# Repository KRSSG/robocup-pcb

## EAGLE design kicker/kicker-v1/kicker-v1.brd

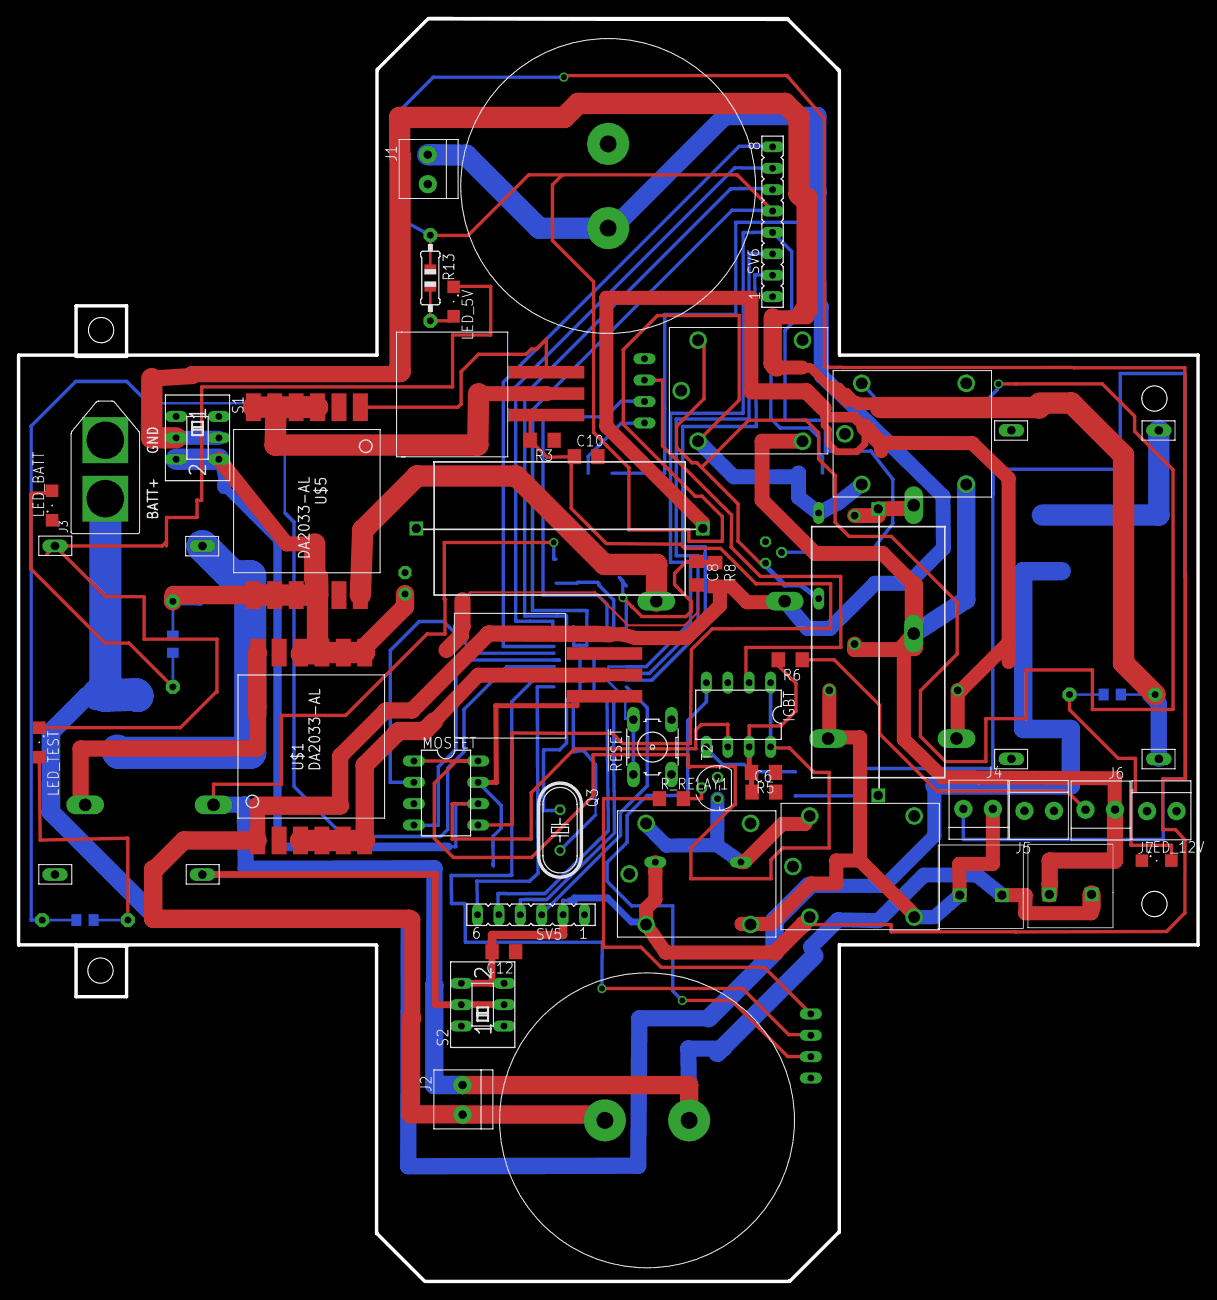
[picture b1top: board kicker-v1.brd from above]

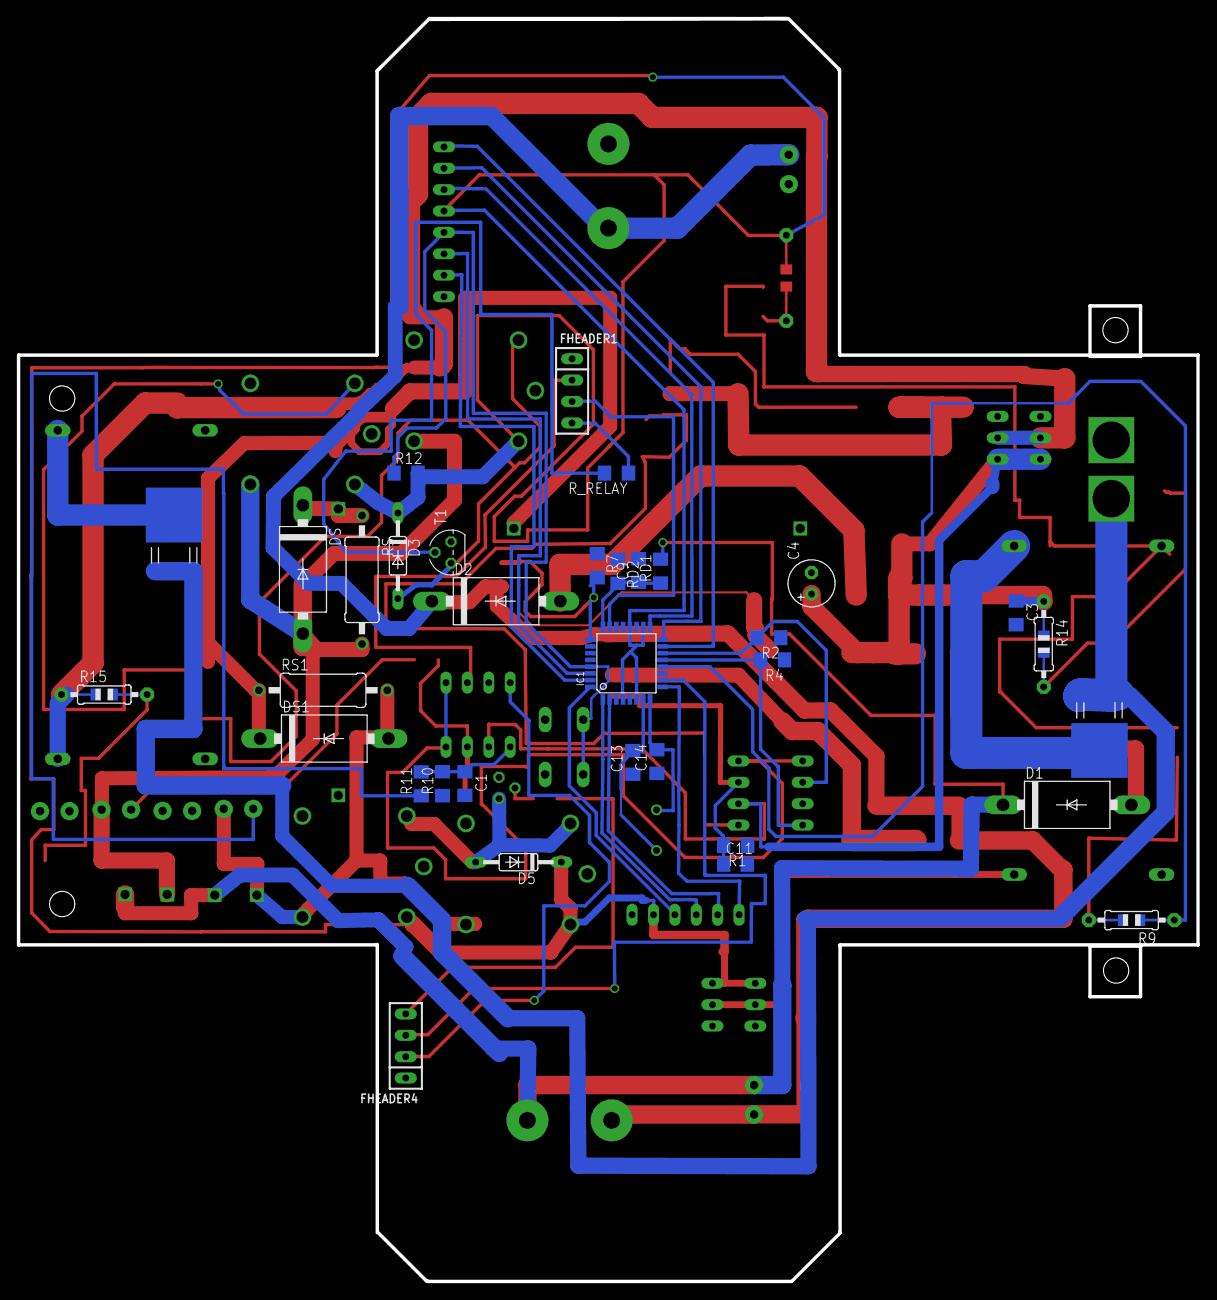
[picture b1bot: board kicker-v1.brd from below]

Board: 2 copper layers, 140.0 x 149.9 mm, 86 parts (34 on the bottom side), 57 nets.

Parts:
5V: PINHEAD_1
!RESET: B3F-10XX
C1, C6, C8, C9, C10, C11: 0.01uF; C1206
C3: 4.7uF; C1206
C4: 4.7uF; E2,5-6
C12: 0.1uF; C1206
C13, C14: 22pF; C1206
D1, D2: UF5400; DO201-15
D3, D5: 1N4446; DO35-10
DS, DS1: UF5400; DO201-15
FHEADER1, FHEADER4: F-1X04-SIP-100-32Y; SIP-100-04-32Y
GND, GND12: PINHEAD_1
GND_5V, GND_12V1: PINHEAD_1
IC1: MEGA8-AI; TQFP32-08
IGBT: NE555; DIL-08
J1, J2, J4, J5, J6, J7: 1X2-3.5MM
J3: XT-60BATT_LABEL; XT-60
LED_5V, LED_12V: SML1206
LED_BATT: SML1206
LED_TEST: SML1206
MOSFET: NE555; DIL-08
POWER_1: PINHEAD_1
POWER_HEAD1: PINHEAD_1
Q3: 16MHz; HC49U70
R1, R3: 1K; R1206
R2, R4, R5, R10, R12: 10K; R1206
R6, R11: 330; R1206
R7: 8.2K; R1206
R8: 1M; R1206
R9, R13: 1 K; 0805-THM
R14, R15: 4.7 K; 0805-THM
RD1: 1M; R1206
RD2: 8.2K; R1206
RS, RS1: 10/.5W; 0411/15
R_RELAY, R_RELAY1: 1K; R1206
S1, S2: A68-A31
SV5: FE06
SV6: FE08
T1, T2: BC547; TO92
U1, U4: TO228P1042X238-3N
U$1, U$5: DA2033-AL
U$2, U$4: CAP
U$3, U$9: MOS
U$6, U$16: SCREW
U$7, U$8: POLYCAP
U$10, U$11, U$12, U$13: REL
V_BAT: PINHEAD_1

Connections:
!RESET: !RESET.1, !RESET.2, IC1.29, R12.1, SV6.4
ATMEGA_POW: C12.2, D3.C, D5.C, IC1.4, IC1.6, IC1.18, IC1.20, R12.2, R13.1, S2.3, S2.6, SV5.2, SV6.5, U$10.2, U$11.2, U$12.2, U$13.2
ATMEGA_POW_BS: 5V.P$1, S2.2, S2.5
BATT: C3.1, C4.+, IGBT.6, MOSFET.6, R14.1, S1.3, S1.6, U$1.P$7, U$1.P$8, U$1.P$9, U$1.P$10, U$5.P$7, U$5.P$8, U$5.P$9, U$5.P$10
C1+: D1.C, J2.1, RD1.2, U$2.P$2, U$6.+, U$16.+
C1-: D2.C, J1.1, J2.2, R8.2, U$1.P$1, U$2.P$1, U$4.P$2
COLLECTOR: D3.A, T1.3, U$10.1, U$12.1
COLLECTOR1: D5.A, T2.3, U$11.1, U$13.1
DRV_IN: J6.2, R6.1
DRV_IN1: J4.2, R11.1
EXT1: IC1.32, SV5.3
EXT2: IC1.1, SV5.4
FEED1: C9.1, IC1.24, RD1.1, RD2.2
FEED2: C8.1, IC1.25, R7.2, R8.1
GND: !RESET.3, !RESET.4, C1.2, C3.2, C4.-, C6.2, C8.2, C9.2, C10.2, C11.2, C12.1, C13.1, C14.1, FHEADER1.1, FHEADER4.1, GND12.P$1, GND_5V.P$1, GND_12V1.P$1, IC1.3, IC1.5, IC1.21, IGBT.3, J1.2, J3.GND, J5.1, J7.1, LED_12V.C, LED_BATT.C, MOSFET.3, R1.1, R2.1, R3.1, R4.1, R5.1, R7.1, R10.1, RD2.1, SV5.1, SV6.1, T1.1, T2.1, U$3.SOURCE, U$4.P$1, U$5.P$1, U$7.2, U$8.2, U$9.SOURCE, U$10.C, U$11.C, U$12.C, U$13.C
GND1: GND.P$1, LED_5V.C, LED_TEST.C
GPIO: IC1.2, SV5.5
GPIO1: IC1.9, SV5.6
IGBT1: FHEADER1.2, IGBT.2
IGBT2: FHEADER4.2, IGBT.4
MISO16: IC1.16, SV6.7
MOS1: IC1.14, MOSFET.2, R2.2
MOS2: IC1.13, MOSFET.4, R4.2
MOSI15: IC1.15, SV6.8
unnamed: DS.C, RS.1, U$7.1
unnamed: R_RELAY.2, T1.2
unnamed: C6.1, IGBT.7, R5.2, R6.2
unnamed: D2.A, U$5.P$12
unnamed: LED_5V.A, R13.2
unnamed: POWER_HEAD1.P$1, U1.2
unnamed: D1.A, U$1.P$12
unnamed: DS1.C, RS1.1, U$8.1
unnamed: R_RELAY1.2, T2.2
unnamed: LED_BATT.A, R14.2
unnamed: C13.2, IC1.7, Q3.2
unnamed: LED_12V.A, R15.2
unnamed: U4.2, V_BAT.P$1
unnamed: C14.2, IC1.8, Q3.1
unnamed: LED_TEST.A, R9.2
unnamed: U$5.P$3, U$5.P$4, U$5.P$5, U$5.P$6, U$9.DRAIN
unnamed: U$1.P$3, U$1.P$4, U$1.P$5, U$1.P$6, U$3.DRAIN
unnamed: IC1.12, R9.1
NC: IGBT.1, IGBT.8, MOSFET.1, MOSFET.8
OUTB: C1.1, IGBT.5, R10.2, R11.2
POWER: POWER_1.P$1, R15.1, S1.2, S1.5
POWER_HEAD: J3.BATT, U1.1, U1.3, U4.1, U4.3
PWM1: C11.1, MOSFET.7, R1.2, U$3.GATE
PWM2: C10.1, MOSFET.5, R3.2, U$9.GATE
RELAY: FHEADER1.4, R_RELAY.1
RELAY1: FHEADER4.4, R_RELAY1.1
RXD30: IC1.30, SV6.3
S1+: DS1.A, J4.1, RS1.2, U$6.-, U$11.NO, U$13.NO
S+: DS.A, J6.1, RS.2, U$10.NO, U$12.NO, U$16.-
SCK17: IC1.17, SV6.6
SWITCH: FHEADER1.3, IC1.23
SWITCH1: FHEADER4.3, IC1.10
TXD31: IC1.31, SV6.2

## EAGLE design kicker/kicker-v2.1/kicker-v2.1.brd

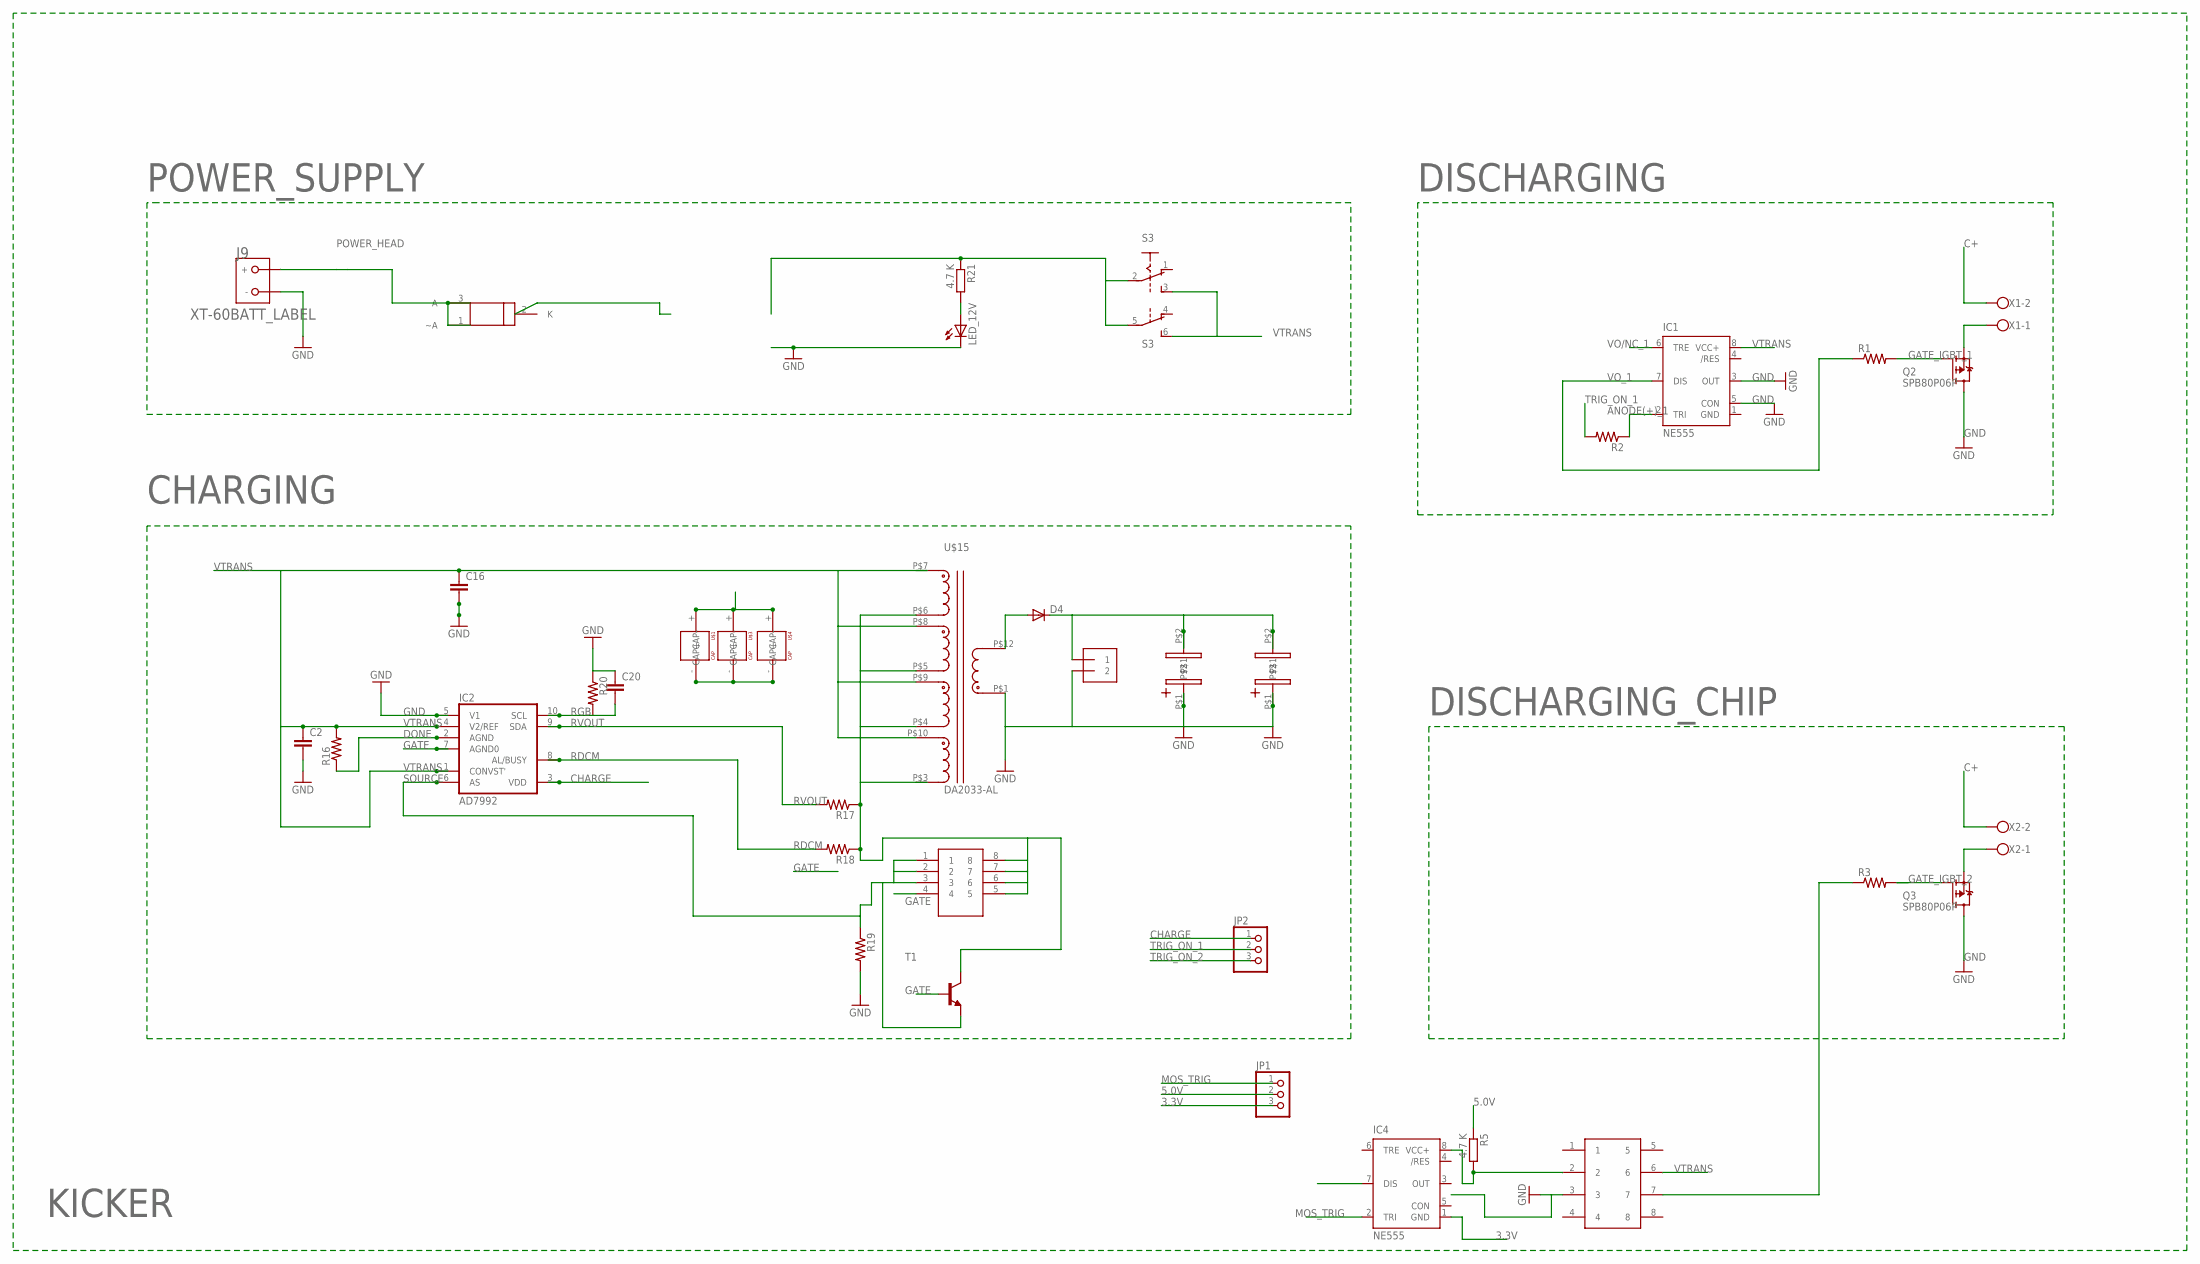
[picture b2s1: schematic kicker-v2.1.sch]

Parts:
C2, C16, C20: C-EUC1206; C1206
D4: DIODE-DO214AA; DO214AA
IC1, IC4: NE555; DIL-08
IC2: AD7992; MSOP10
J8: 1X2-3.5MM
J9: XT-60BATT_LABEL; XT-60
JP1, JP2: PINHD-1X3; 1X03
LED_12V: LEDSML1206; SML1206
Q2, Q3: SPB80P06P; TO263
R1, R2, R3, R16, R17, R18, R19, R20: R-US_R1206; R1206
R5, R21: 4.7 K; 0207/10
S3: A68-A31
T1: -NPN-SOT223; SOT223
U1: LP38690DT-3.3; TO228P1042X238-3N
U$1, U$3, U$4: CAP; SVP_F12
U$2, U$17: CAPS; CAP
U$5: MOSFET-LT3750; SON-8
U$6: TC4426A; SOIC-8
U$15: DA2033-AL
X1, X2: W237-102

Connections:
3.3V: IC4.1 (GND), JP1.3
5.0V: JP1.2, R5.1
ANODE(+)_1: IC1.2 (TRI), R2.1
C+: D4.C, J8.1, U$2.P$2, U$17.P$2, X1.2, X2.2
CHARGE: IC2.3 (VDD), JP2.1
DONE: IC2.2 (AGND), R16.1
GATE: IC2.7 (AGND0), T1.1 (B), U$5.4
GATE_IGBT_1: Q2.1 (G), R1.2
GATE_IGBT_2: Q3.1 (G), R3.2
GND: C2.2, C16.2, C20.1, IC1.1 (GND), IC1.3 (OUT), IC1.5 (CON), IC2.5 (V1), J8.2, J9.GND (-), LED_12V.C, Q2.3 (D), Q3.3 (D), R19.2, R20.1, U$1.- (CAP-), U$2.P$1, U$3.- (CAP-), U$4.- (CAP-), U$15.P$1 (1), U$17.P$1
MOS_TRIG: IC4.2 (TRI), JP1.1
unnamed: Q2.2 (S), X1.1
unnamed: Q3.2 (S), X2.1
unnamed: R17.1, R18.1, T1.4 (C), U$5.5, U$5.6, U$5.7, U$5.8, U$15.P$3 (3), U$15.P$4 (4), U$15.P$5 (5), U$15.P$6 (6)
unnamed: IC4.8 (VCC+), R5.2, U$6.2
unnamed: D4.A, U$15.P$12 (12)
unnamed: LED_12V.A, R21.2
PIN3: IC4.7 (DIS), U$6.3
POWER_HEAD: J9.BATT (+), U1.1 (~A), U1.3 (A)
RDCM: IC2.8 (AL/BUSY), R18.2
RGB: C20.2, IC2.10 (SCL), R20.2
RVOUT: IC2.9 (SDA), R17.2
SOURCE: IC2.6 (AS), R19.1, T1.3 (E), U$5.1, U$5.2, U$5.3
SUPP_+: R21.1, S3.2, S3.5, U1.2 (K)
TRIG_ON_1: JP2.2, R2.2
TRIG_ON_2: JP2.3
VO/NC_1: IC1.6 (TRE)
VO_1: IC1.7 (DIS), R1.1
VO_2: R3.1, U$6.7
VTRANS: C2.1, C16.1, IC1.8 (VCC+), IC2.1 (CONVST'), IC2.4 (V2/REF), R16.2, S3.3 (S), S3.6 (S), U$1.+ (CAP+), U$3.+ (CAP+), U$4.+ (CAP+), U$6.6, U$15.P$7 (7), U$15.P$8 (8), U$15.P$9 (9), U$15.P$10 (10)

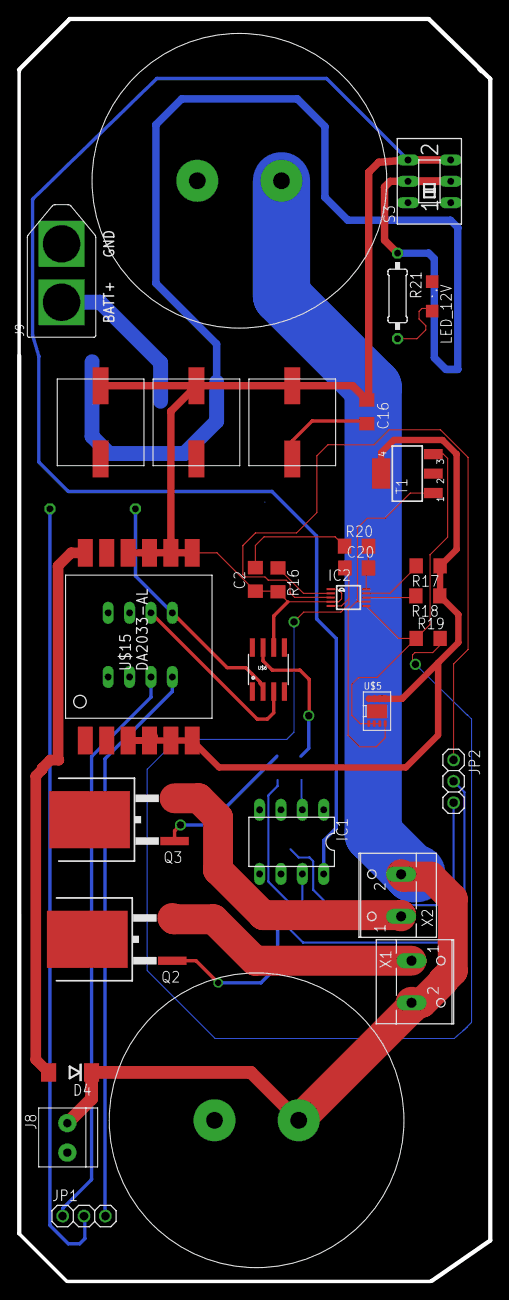
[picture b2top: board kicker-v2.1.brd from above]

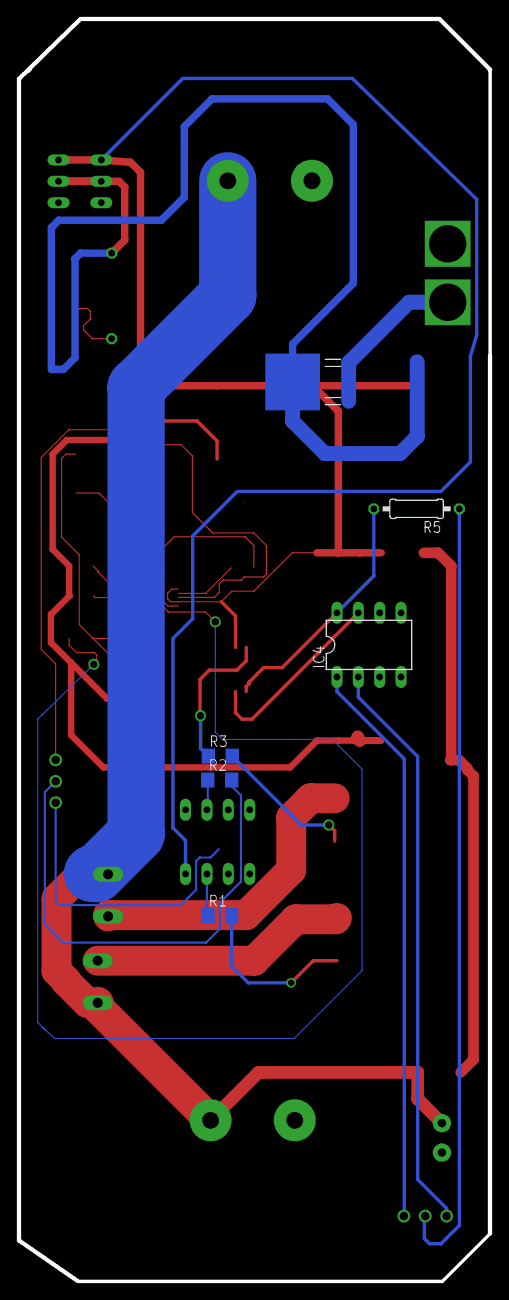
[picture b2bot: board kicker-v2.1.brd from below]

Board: 2 copper layers, 56.0 x 149.9 mm, 37 parts (6 on the bottom side), 28 nets.

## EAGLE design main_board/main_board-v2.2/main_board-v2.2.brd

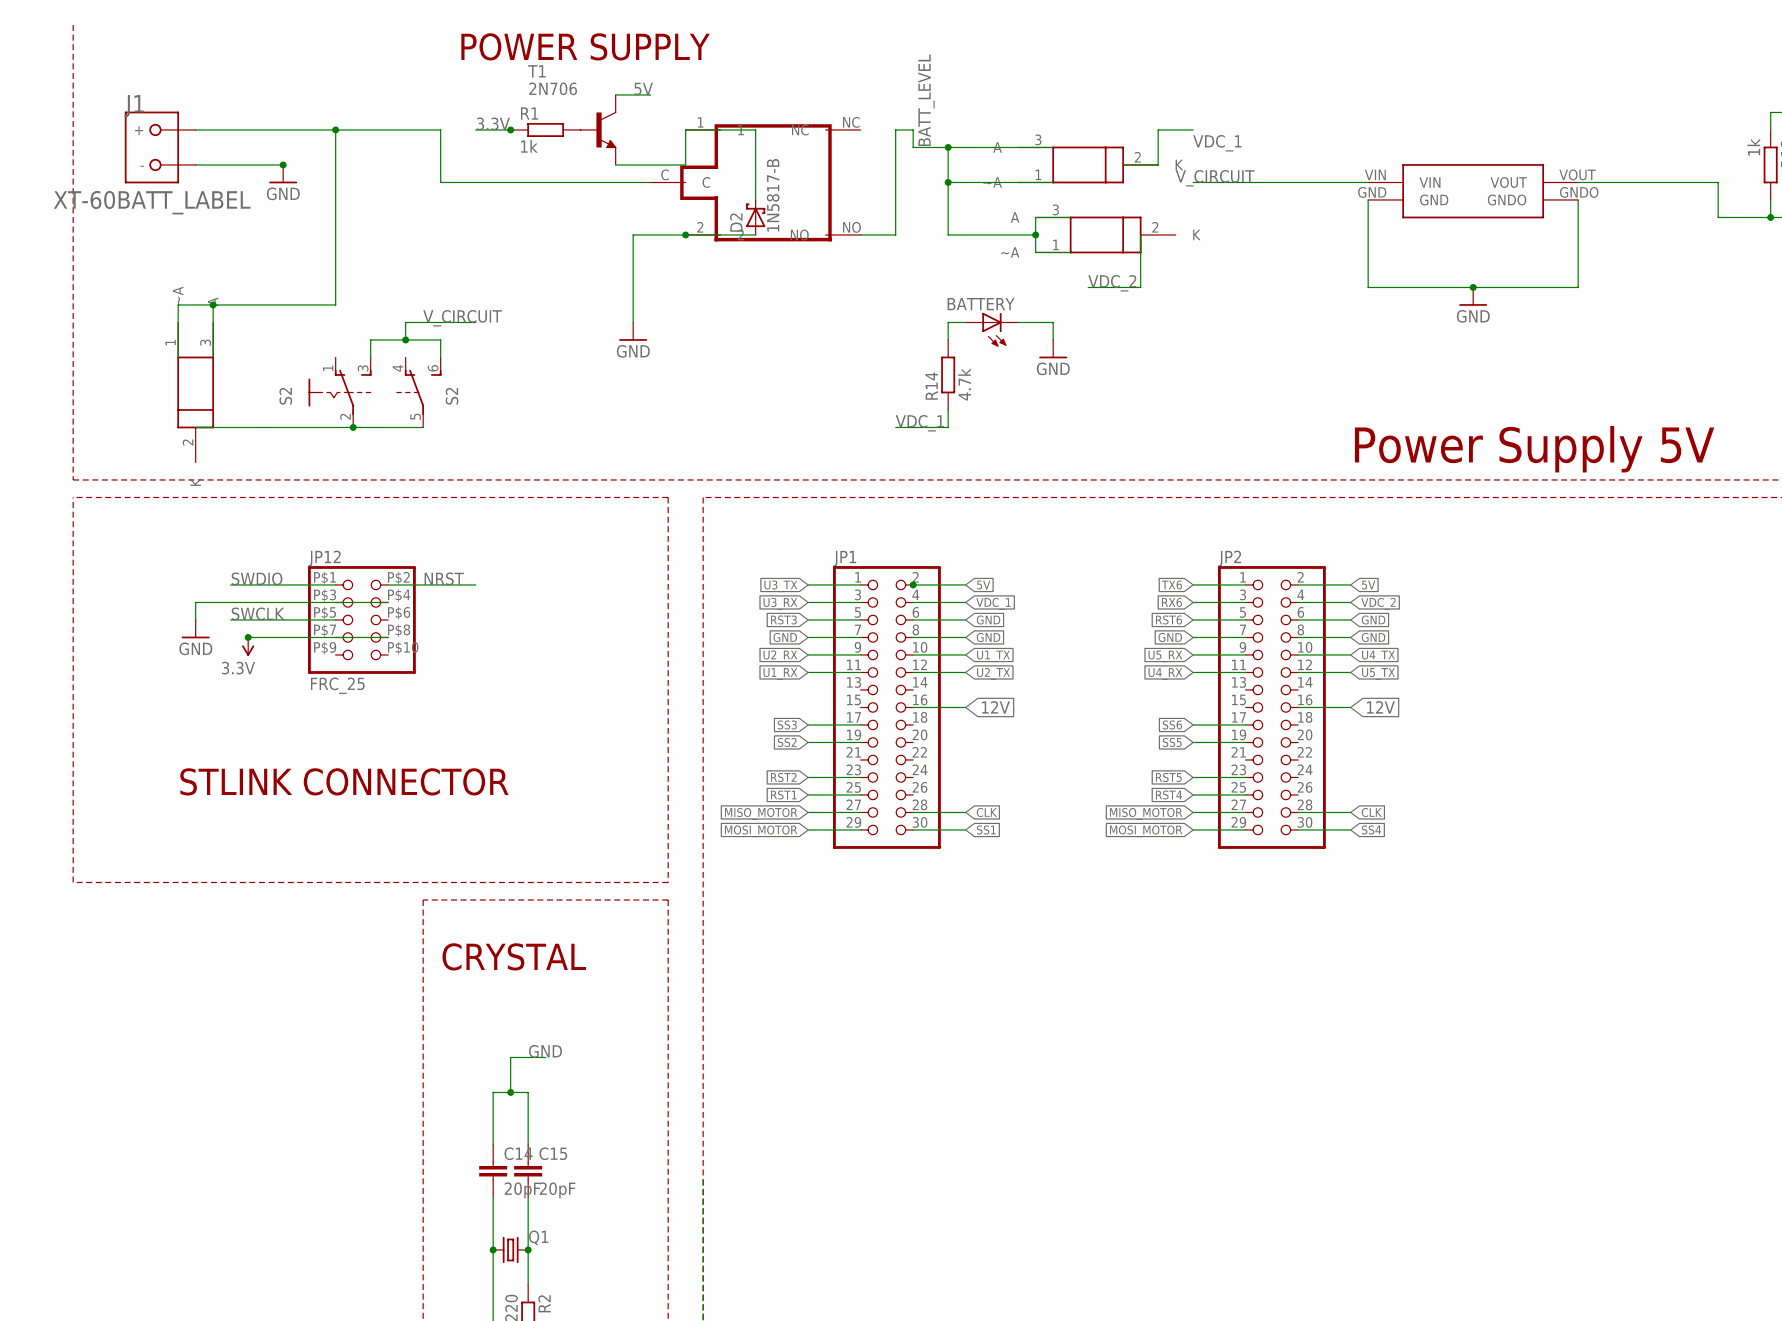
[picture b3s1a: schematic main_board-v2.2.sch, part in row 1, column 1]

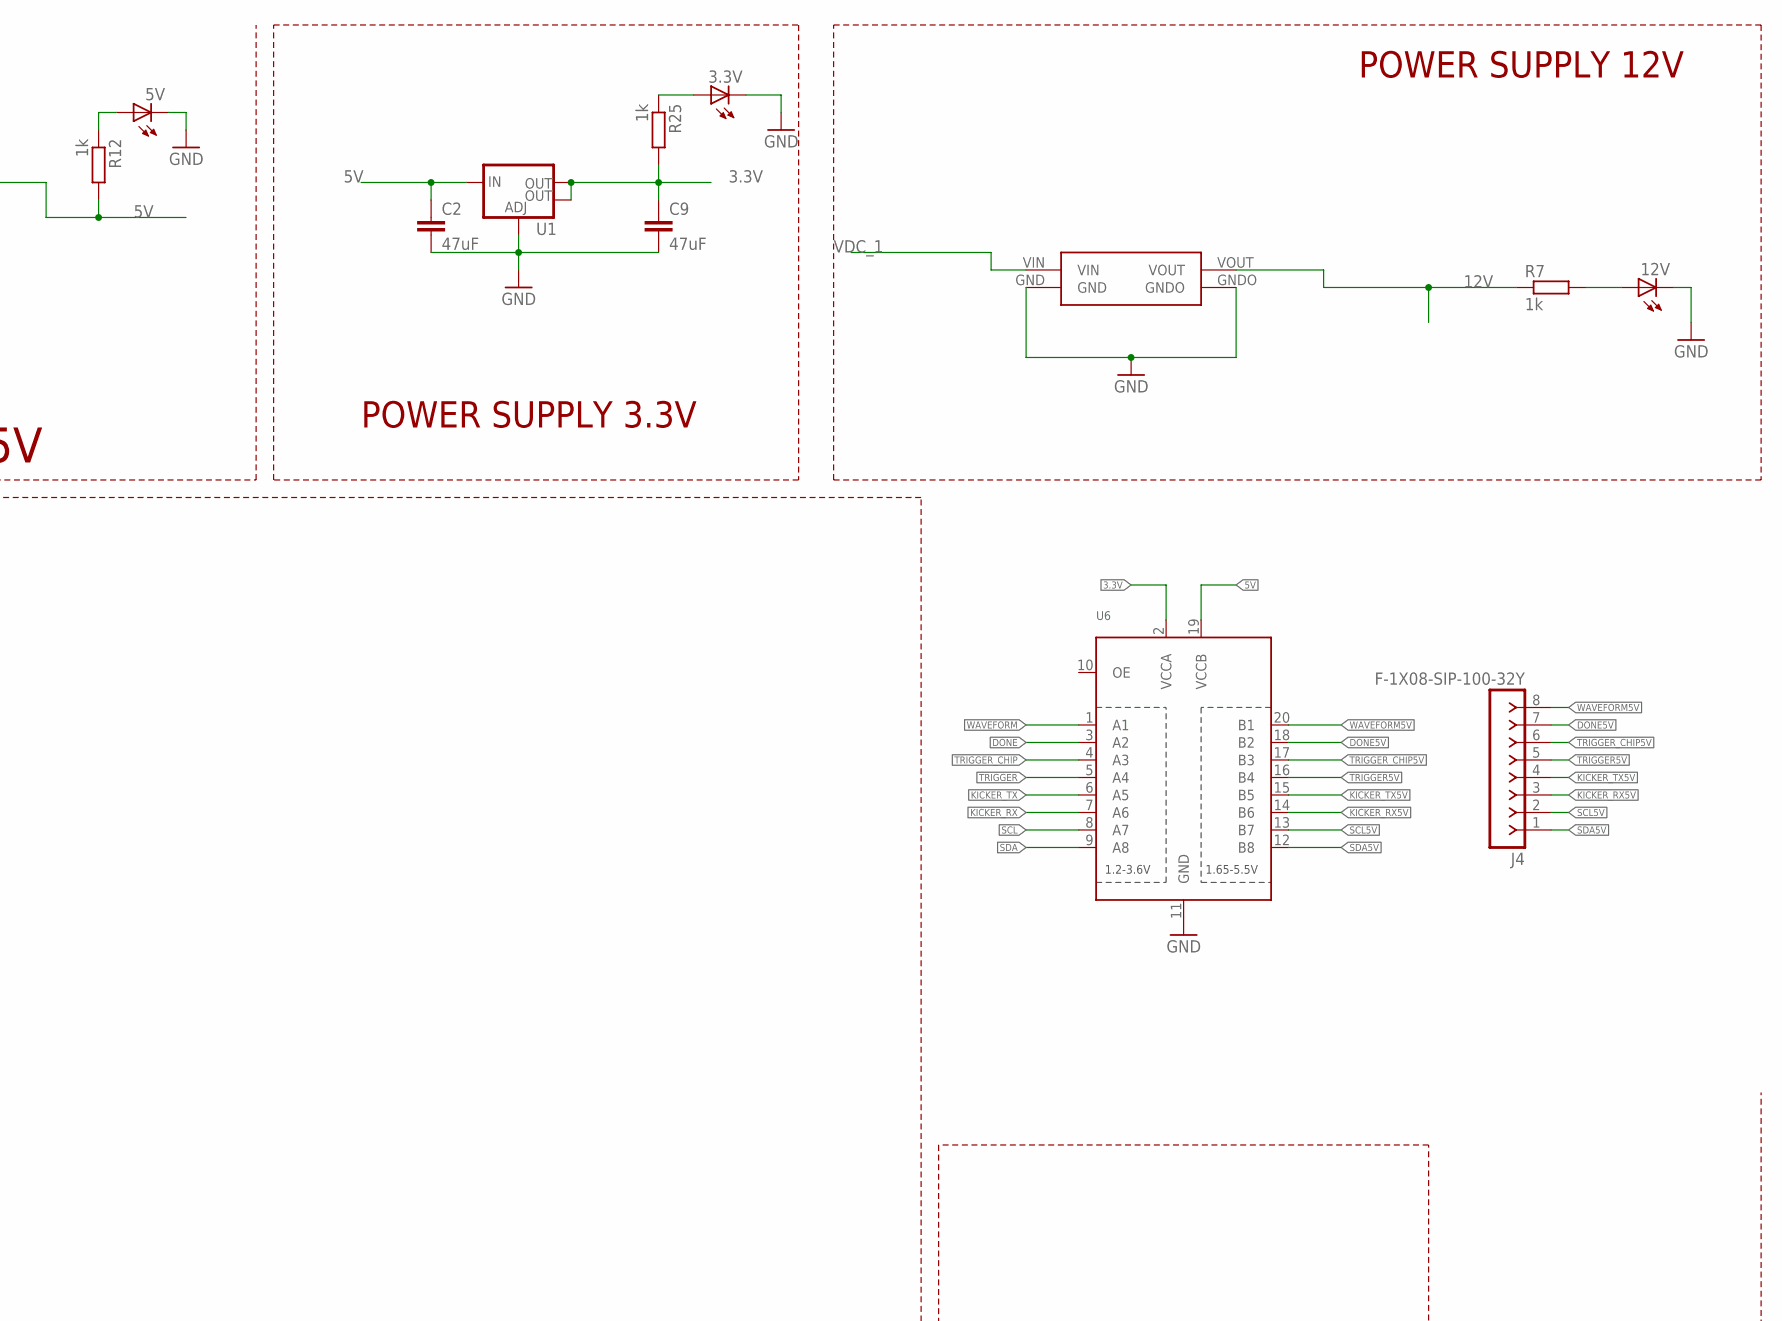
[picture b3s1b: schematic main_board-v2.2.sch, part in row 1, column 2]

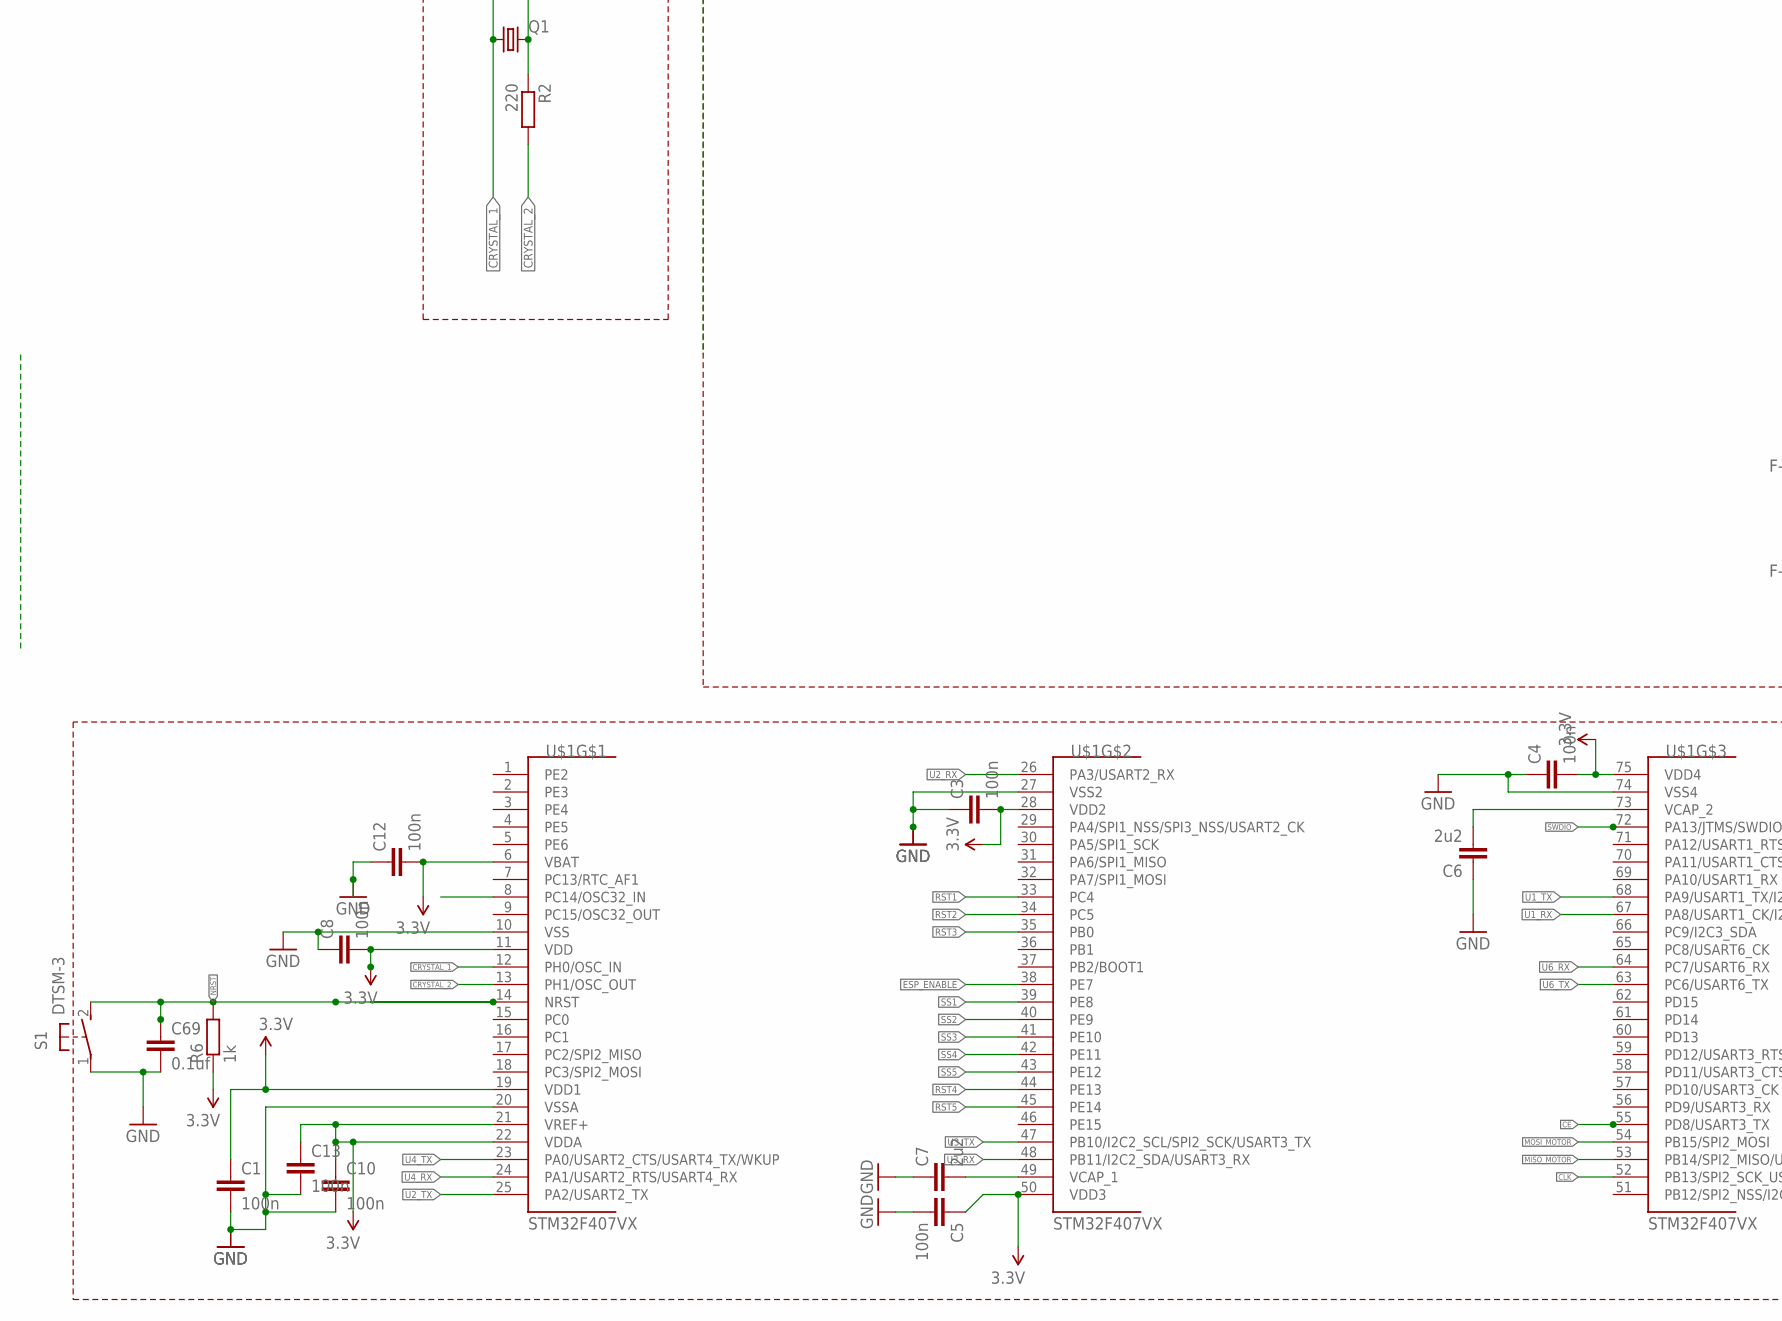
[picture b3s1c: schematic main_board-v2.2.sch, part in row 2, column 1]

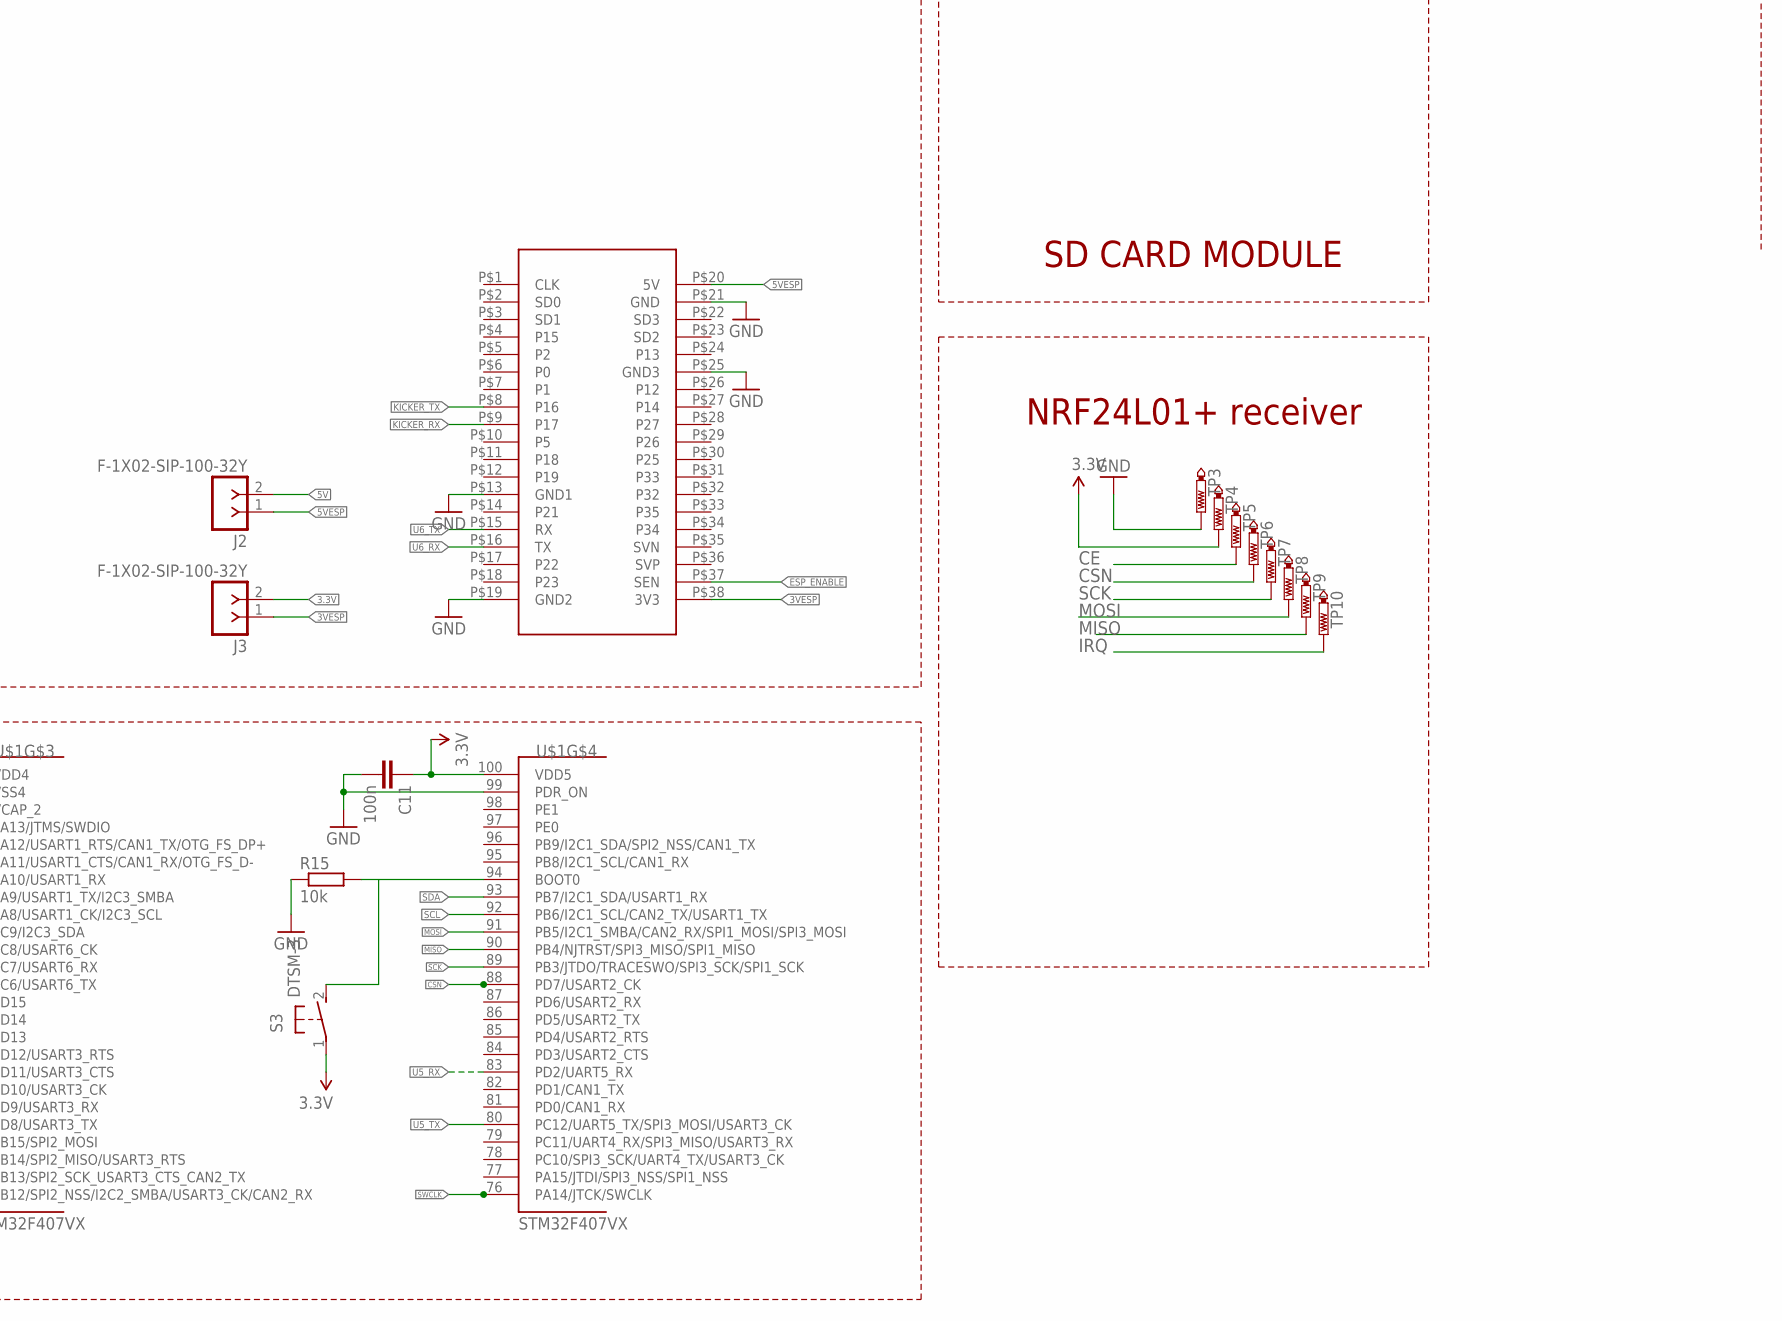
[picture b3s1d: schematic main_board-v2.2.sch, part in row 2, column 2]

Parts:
3.3V, 5V, 12V: LEDCHIPLED_0805; CHIPLED_0805
BATTERY: LEDCHIPLED_0805; CHIPLED_0805
C1, C3, C4, C5, C8, C10, C11, C12, C13: 100n; C1206
C2, C9: 47uF; C1206
C6, C7: 2u2; C1206
C14, C15: 20pF; C1206
C69: 0.1uf; C1206
D2: 1N5817-B; DO41-7.6
J1: XT-60BATT_LABEL; XT-60
J2, J3: F-1X02-SIP-100-32Y; SIP-100-02-32Y
J4: F-1X08-SIP-100-32Y; SIP-100-08-32Y
JP1, JP2: PINHD-2X15_2.54; 2X15
JP12: FRC_25; FRC2*5
Q1: CRYSTALHC49U-V; HC49U-V
R1, R6, R7, R12, R25: 1k; R1206
R2: 220; R1206
R14: 4.7k; R1206
R15: 10k; R1206
S1, S3: DTSM-3
S2: A68-A31
T1: 2N706; TO18
TP3, TP4, TP5, TP6, TP7, TP8, TP9, TP10: PTR1PAD1-13; P1-13
U1: V_REG_LM1117SOT223; SOT223
U2, U3, U4: LP38690DT-3.3; TO228P1042X238-3N
U6: TXB0108PWR; TSSOP20
U$1: STM32F407VX; LQFP100
U$2: REL
U$3, U$4: BUCK
U$6: NODEMCU32S; NODEMCU32

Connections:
3.3V: C1.1, C3.2, C4.2, C5.1, C8.2, C9.1, C10.1, C11.1, C12.2, C13.1, J3.2, JP12.P$7 (7), JP12.P$8 (8), R1.1, R6.1, R25.2, S3.1, TP4.TP, U1.2 (OUT), U1.4 (OUT), U6.2 (VCCA), U$1.6 (VBAT), U$1.11 (VDD), U$1.19 (VDD1), U$1.21 (VREF+), U$1.22 (VDDA), U$1.28 (VDD2), U$1.50 (VDD3), U$1.75 (VDD4), U$1.100 (VDD5)
3VESP: J3.1, U$6.P$38 (3V3)
5V: C2.1, J2.2, JP1.2, JP2.2, R12.2, T1.3 (C), U1.3 (IN), U6.19 (VCCB), U$3.VOUT
5VESP: J2.1, U$6.P$20 (5V)
12V: JP1.16, JP2.16, R7.1, U$4.VOUT
BATT_LEVEL: U2.1 (~A), U2.3 (A), U4.1 (~A), U4.3 (A), U$2.NO
CE: TP5.TP, U$1.55 (PD8/USART3_TX)
CLK: JP1.28, JP2.28, U$1.52 (PB13/SPI2_SCK_USART3_CTS_CAN2_TX)
CRYSTAL_1: C14.2, Q1.1, U$1.12 (PH0/OSC_IN)
CRYSTAL_2: R2.2, U$1.13 (PH1/OSC_OUT)
CSN: TP6.TP, U$1.88 (PD7/USART2_CK)
DONE: U6.3 (A2)
DONE5V: J4.7, U6.18 (B2)
ESP_ENABLE: U$1.38 (PE7), U$6.P$37 (SEN)
GND: 3.3V.C, 5V.C, 12V.C, BATTERY.C, C1.2, C2.2, C3.1, C4.1, C5.2, C6.1, C7.1, C8.1, C9.2, C10.2, C11.2, C12.1, C13.2, C14.1, C15.1, C69.2, D2.A, J1.GND (-), JP1.6, JP1.7, JP1.8, JP2.6, JP2.7, JP2.8, JP12.P$3 (3), JP12.P$4 (4), R15.1, S1.1, TP3.TP, U1.1 (ADJ), U6.11 (GND), U$1.10 (VSS), U$1.20 (VSSA), U$1.27 (VSS2), U$1.74 (VSS4), U$1.99 (PDR_ON), U$2.2, U$3.GND, U$3.GNDO, U$4.GND, U$4.GNDO, U$6.P$13 (GND1), U$6.P$19 (GND2), U$6.P$21 (GND), U$6.P$25 (GND3)
INPUT: J1.BATT (+), U3.1 (~A), U3.3 (A), U$2.C
IRQ: TP10.TP
IRQ_SPI2: U$1.8 (PC14/OSC32_IN)
KICKER_RX: U6.7 (A6), U$6.P$9 (P17)
KICKER_RX5V: J4.3, U6.14 (B6)
KICKER_TX: U6.6 (A5), U$6.P$8 (P16)
KICKER_TX5V: J4.4, U6.15 (B5)
MISO: TP9.TP, U$1.90 (PB4/NJTRST/SPI3_MISO/SPI1_MISO)
MISO_MOTOR: JP1.27, JP2.27, U$1.53 (PB14/SPI2_MISO/USART3_RTS)
MOSI: TP8.TP, U$1.91 (PB5/I2C1_SMBA/CAN2_RX/SPI1_MOSI/SPI3_MO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)
MOSI_MOTOR: JP1.29, JP2.29, U$1.54 (PB15/SPI2_MOSI)
unnamed: C7.2, U$1.49 (VCAP_1)
unnamed: C6.2, U$1.73 (VCAP_2)
unnamed: R15.2, S3.2, U$1.94 (BOOT0)
unnamed: C15.2, Q1.2, R2.1
unnamed: 5V.A, R12.1
unnamed: 12V.A, R7.2
unnamed: BATTERY.A, R14.2
unnamed: 3.3V.A, R25.1
unnamed: R1.2, T1.2 (B)
unnamed: D2.C, T1.1 (E), U$2.1
unnamed: S2.2, S2.5, U3.2 (K)
NRST: C69.1, JP12.P$2 (2), R6.2, S1.2, U$1.14 (NRST)
RST1: JP1.25, U$1.33 (PC4)
RST2: JP1.23, U$1.34 (PC5)
RST3: JP1.5, U$1.35 (PB0)
RST4: JP2.25, U$1.44 (PE13)
RST5: JP2.23, U$1.45 (PE14)
RST6: JP2.5
RX6: JP2.3
SCK: TP7.TP, U$1.89 (PB3/JTDO/TRACESWO/SPI3_SCK/SPI1_SCK)
SCL: U6.8 (A7), U$1.92 (PB6/I2C1_SCL/CAN2_TX/USART1_TX)
SCL5V: J4.2, U6.13 (B7)
SDA: U6.9 (A8), U$1.93 (PB7/I2C1_SDA/USART1_RX)
SDA5V: J4.1, U6.12 (B8)
SS1: JP1.30, U$1.39 (PE8)
SS2: JP1.19, U$1.40 (PE9)
SS3: JP1.17, U$1.41 (PE10)
SS4: JP2.30, U$1.42 (PE11)
SS5: JP2.19, U$1.43 (PE12)
SS6: JP2.17
SWCLK: JP12.P$5 (5), U$1.76 (PA14/JTCK/SWCLK)
SWDIO: JP12.P$1 (1), U$1.72 (PA13/JTMS/SWDIO)
TRIGGER: U6.5 (A4)
TRIGGER5V: J4.5, U6.16 (B4)
TRIGGER_CHIP: U6.4 (A3)
TRIGGER_CHIP5V: J4.6, U6.17 (B3)
TX6: JP2.1
U1_RX: JP1.11, U$1.67 (PA8/USART1_CK/I2C3_SCL)
U1_TX: JP1.10, U$1.68 (PA9/USART1_TX/I2C3_SMBA)
U2_RX: JP1.9, U$1.26 (PA3/USART2_RX)
U2_TX: JP1.12, U$1.25 (PA2/USART2_TX)
U3_RX: JP1.3, U$1.48 (PB11/I2C2_SDA/USART3_RX)
U3_TX: JP1.1, U$1.47 (PB10/I2C2_SCL/SPI2_SCK/USART3_TX)
U4_RX: JP2.11, U$1.24 (PA1/USART2_RTS/USART4_RX)
U4_TX: JP2.10, U$1.23 (PA0/USART2_CTS/USART4_TX/WKUP)
U5_RX: JP2.9, U$1.83 (PD2/UART5_RX)
U5_TX: JP2.12, U$1.80 (PC12/UART5_TX/SPI3_MOSI/USART3_CK)
U6_RX: U$1.64 (PC7/USART6_RX), U$6.P$16 (TX)
U6_TX: U$1.63 (PC6/USART6_TX), U$6.P$15 (RX)
VDC_1: JP1.4, R14.1, U4.2 (K), U$4.VIN
VDC_2: JP2.4, U2.2 (K)
V_CIRCUIT: S2.3 (S), S2.6 (S), U$3.VIN
WAVEFORM: U6.1 (A1)
WAVEFORM5V: J4.8, U6.20 (B1)

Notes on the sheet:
NRF24L01+ receiver
STLINK CONNECTOR
POWER SUPPLY 12V
POWER SUPPLY 3.3V
POWER SUPPLY
Power Supply 5V
CRYSTAL
SD CARD MODULE

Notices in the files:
parts and their libraries:
con-headers-jp: Copyright (C) 2008, Bob Starr
SparkFun: Licensing: CC v3.0 Share-Alike You are welcome to use this library for commercial purposes.
SparkFun-PowerIC: Licensing: Creative Commons ShareAlike 4.0 International - https://creativecommons.org/licenses/by-sa/4.0
